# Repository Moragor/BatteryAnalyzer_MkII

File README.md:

# BatteryAnalyzer_MkII
Updated Version of the battery analyzer, now with constant current testing instead of fixed resistors.

## Features:
- Selectable test current
- Support for Alkaline/LiFeS2, NiMh and Li-Ion/LiPo (1S) batteries
- Optional datalogging for voltage, current, power, capacity and energy with .csv output on microSD card

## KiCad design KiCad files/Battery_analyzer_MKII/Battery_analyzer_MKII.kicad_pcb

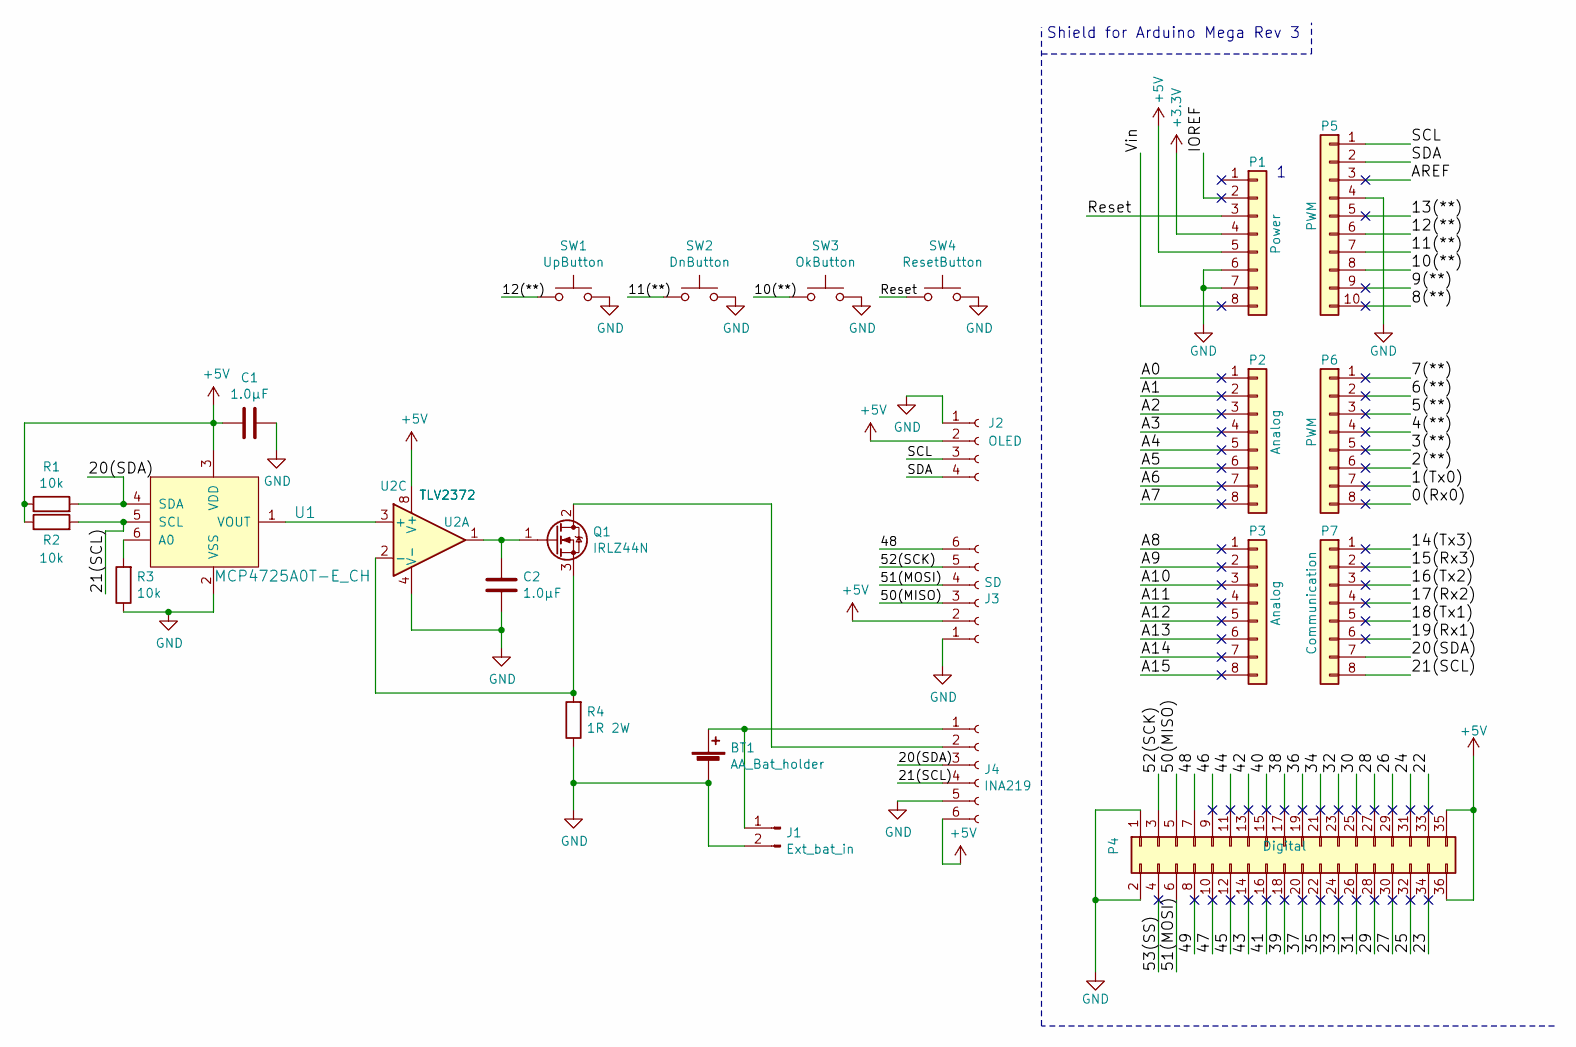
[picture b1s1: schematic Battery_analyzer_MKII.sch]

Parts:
BT1: AA_Bat_holder; AA_Battery_holder_L57mm_W17mm
C1, C2: 1.0µF; C_Disc_D5.5mm_W2.7mm_P5.5mm
J1: Ext_bat_in; PinHeader_1x02_P2.54mm_Vertical
J2: OLED; PinSocket_1x04_P2.54mm_Vertical
J3: SD; PinSocket_1x06_P2.54mm_Horizontal
J4: INA219; PinSocket_1x06_P2.54mm_Vertical
P1: Power; PinHeader_1x08_P2.54mm_Vertical
P2, P3: Analog; PinHeader_1x08_P2.54mm_Vertical
P4: Digital; PinHeader_2x18_P2.54mm_Vertical
P5: PWM; PinHeader_1x10_P2.54mm_Vertical
P6: PWM; PinHeader_1x08_P2.54mm_Vertical
P7: Communication; PinHeader_1x08_P2.54mm_Vertical
Q1: IRLZ44N; TO-220-3_Vertical
R1, R2, R3: 10k; R_Axial_DIN0207_L6.3mm_D2.5mm_P10.16mm_Horizontal
R4: 1R 2W; R_Axial_DIN0411_L9.9mm_D3.6mm_P15.24mm_Horizontal
SW1: UpButton; SW_PUSH_6mm_H5mm
SW2: DnButton; SW_PUSH_6mm_H5mm
SW3: OkButton; SW_PUSH_6mm_H5mm
SW4: ResetButton; SW_PUSH_6mm_H5mm
U1: MCP4725A0T-E_CH; SOT-23-6_Handsoldering; MPN MCP4725A0T-E/CH; Digi-Key_PN MCP4725A0T-E/CHCT-ND
U2: TLV2372; DIP-8_W7.62mm_Socket

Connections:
+3V3: P1.4
+5V: C1.2, J2.2, J3.2, J4.6, P1.5, P4.35, P4.36, R1.1, R2.1, U1.3 (VDD), U2.8 (V+)
/0(Rx0): P6.8
/1(Tx0): P6.7
/2(**): P6.6
/3(**): P6.5
/4(**): P6.4
/5(**): P6.3
/6(**): P6.2
/7(**): P6.1
/8(**): P5.10
/9(**): P5.9
/10(**): P5.8, SW3.1
/11(**): P5.7, SW2.1
/12(**): P5.6, SW1.1
/13(**): P5.5
/14(Tx3): P7.1
/15(Rx3): P7.2
/16(Tx2): P7.3
/17(Rx2): P7.4
/18(Tx1): P7.5
/19(Rx1): P7.6
/20(SDA): J4.3, P7.7, R1.2, U1.4 (SDA)
/21(SCL): J4.4, P7.8, R2.2, U1.5 (SCL)
/22: P4.33
/23: P4.34
/24: P4.31
/25: P4.32
/26: P4.29
/27: P4.30
/28: P4.27
/29: P4.28
/30: P4.25
/31: P4.26
/32: P4.23
/33: P4.24
/34: P4.21
/35: P4.22
/36: P4.19
/37: P4.20
/38: P4.17
/39: P4.18
/40: P4.15
/41: P4.16
/42: P4.13
/43: P4.14
/44: P4.11
/45: P4.12
/46: P4.9
/47: P4.10
/48: J3.6, P4.7
/49: P4.8
/50(MISO): J3.3, P4.5
/51(MOSI): J3.4, P4.6
/52(SCK): J3.5, P4.3
/53(SS): P4.4
/A0: P2.1
/A1: P2.2
/A2: P2.3
/A3: P2.4
/A4: P2.5
/A5: P2.6
/A6: P2.7
/A7: P2.8
/A8: P3.1
/A9: P3.2
/A10: P3.3
/A11: P3.4
/A12: P3.5
/A13: P3.6
/A14: P3.7
/A15: P3.8
/AREF: P5.3
/IOREF: P1.2
/Reset: P1.3, SW4.1
/SCL: J2.3, P5.1
/SDA: J2.4, P5.2
/Vin: P1.8
GND: BT1.2 (-), C1.1, C2.1, J1.2, J2.1, J3.1, J4.5, P1.6, P1.7, P4.1, P4.2, P5.4, R3.1, R4.1, SW1.2, SW2.2, SW3.2, SW4.2, U1.2 (VSS), U2.4 (V-)
unnamed: BT1.1 (+), J1.1, J4.1
unnamed: C2.2, Q1.1 (G), U2.1
unnamed: J4.2, Q1.2 (D)
unnamed: Q1.3 (S), R4.2, U2.2 (-)
unnamed: R3.2, U1.6 (A0)
unnamed: U1.1 (VOUT), U2.3 (+)

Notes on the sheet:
Shield for Arduino Mega Rev 3

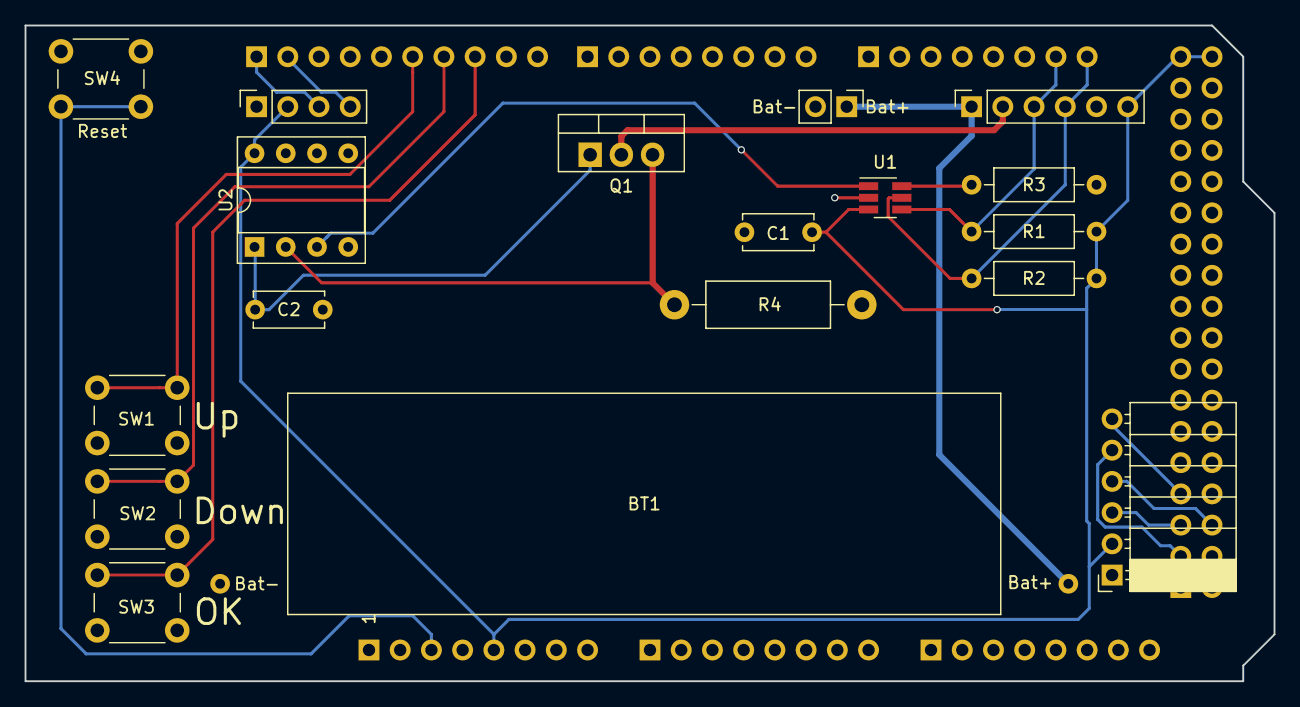
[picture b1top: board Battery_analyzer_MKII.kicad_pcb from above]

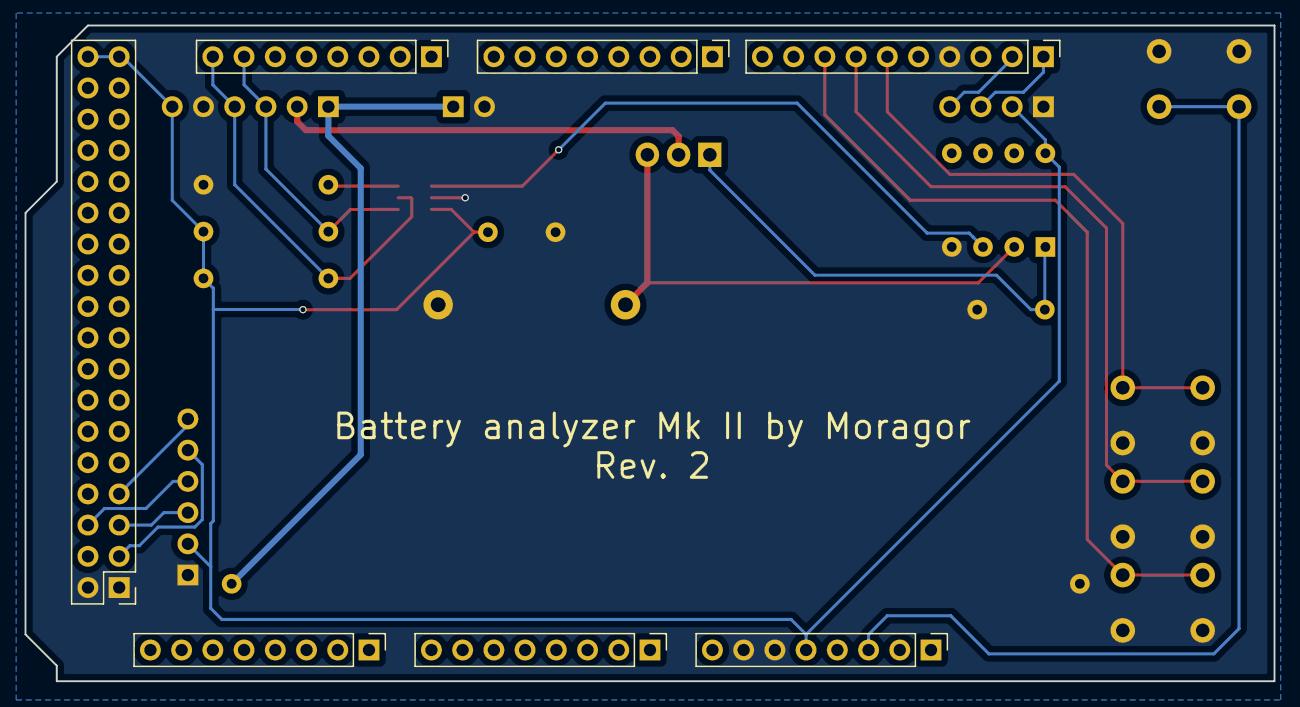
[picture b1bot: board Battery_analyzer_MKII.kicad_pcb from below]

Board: 2 copper layers, 101.6 x 53.3 mm, 25 parts (7 on the bottom side), 20 nets.

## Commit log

2021-04-06 Initial edit
    Readme update, files added
2021-04-06 Fixed a typo
2021-04-10 Adding more files
